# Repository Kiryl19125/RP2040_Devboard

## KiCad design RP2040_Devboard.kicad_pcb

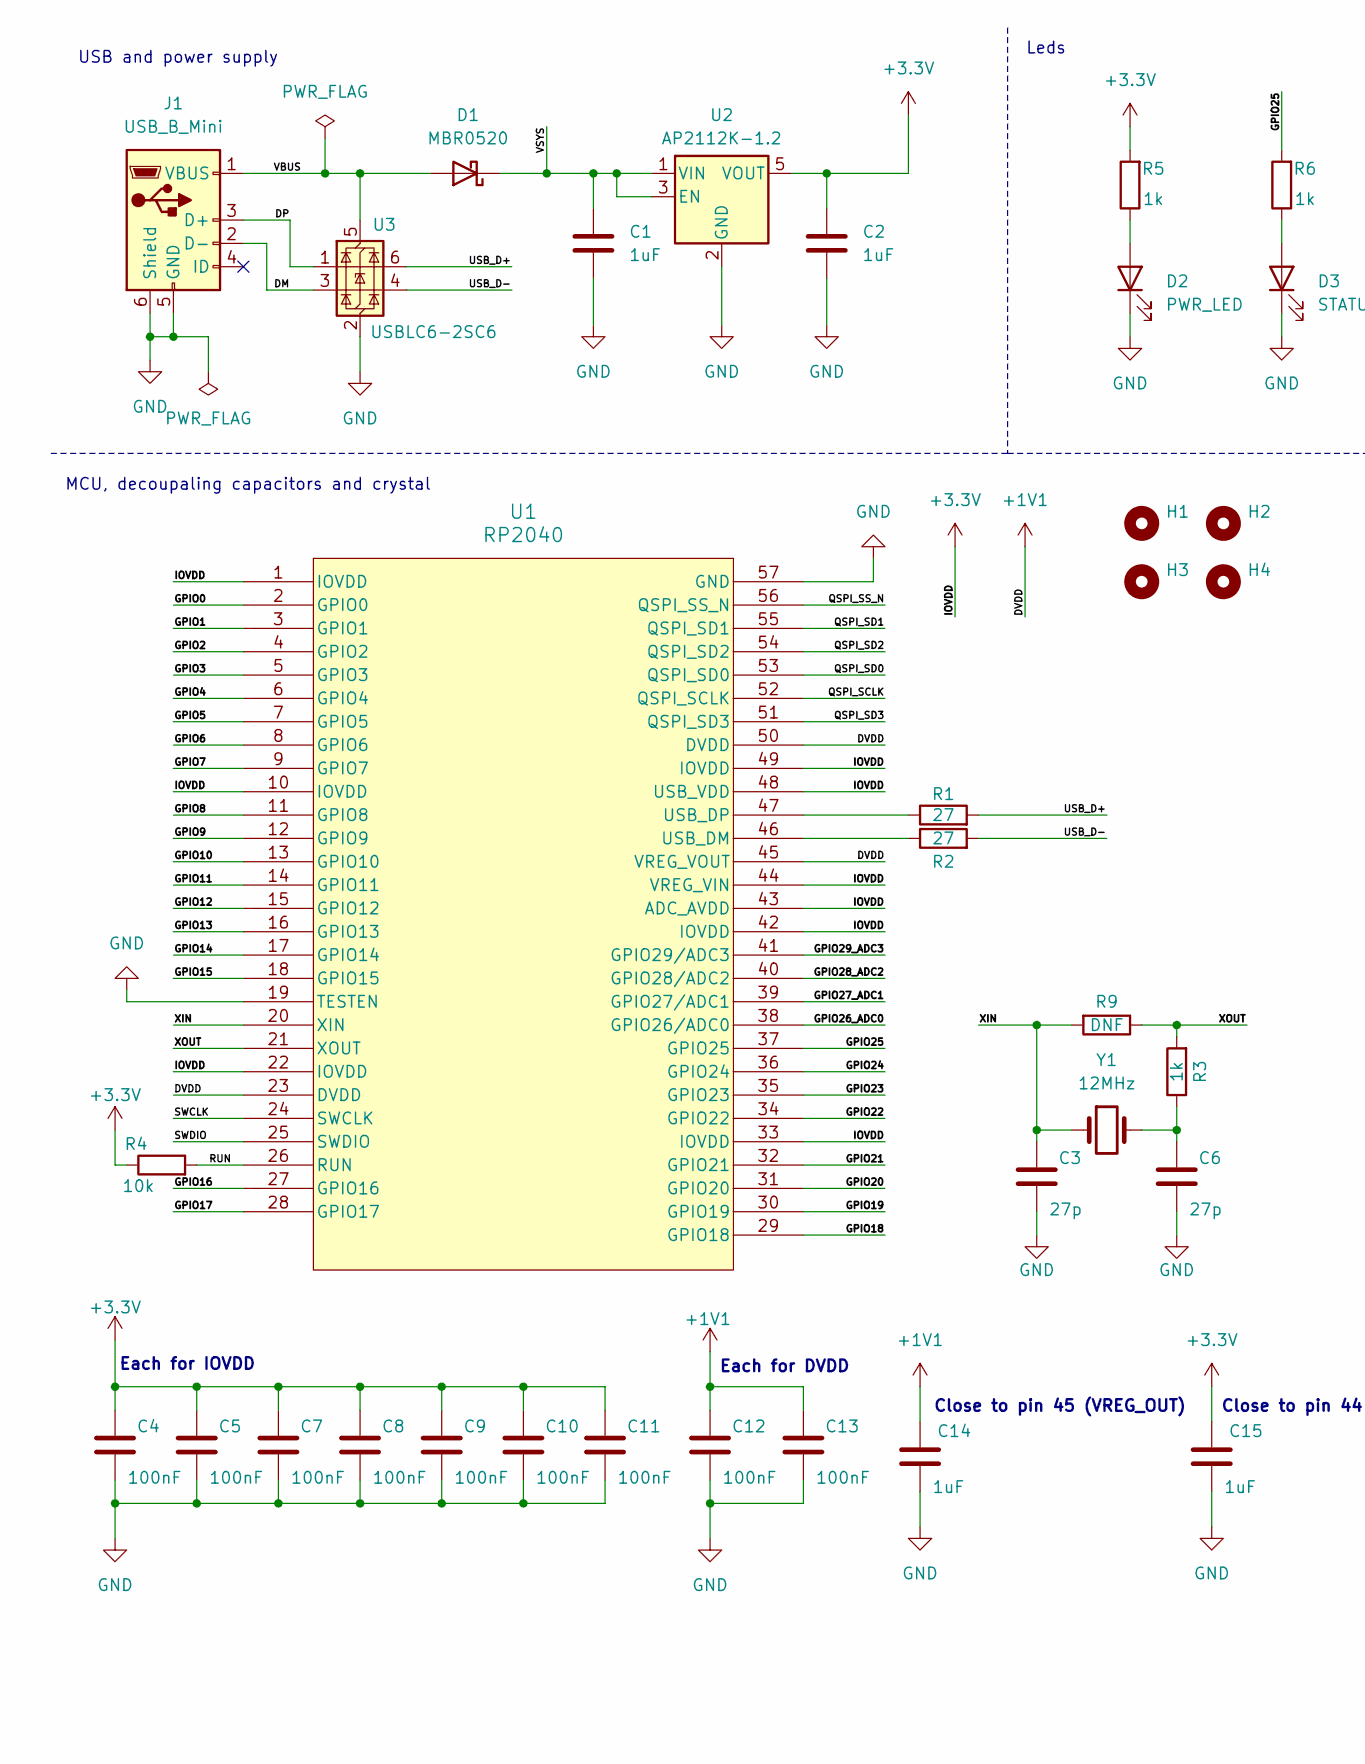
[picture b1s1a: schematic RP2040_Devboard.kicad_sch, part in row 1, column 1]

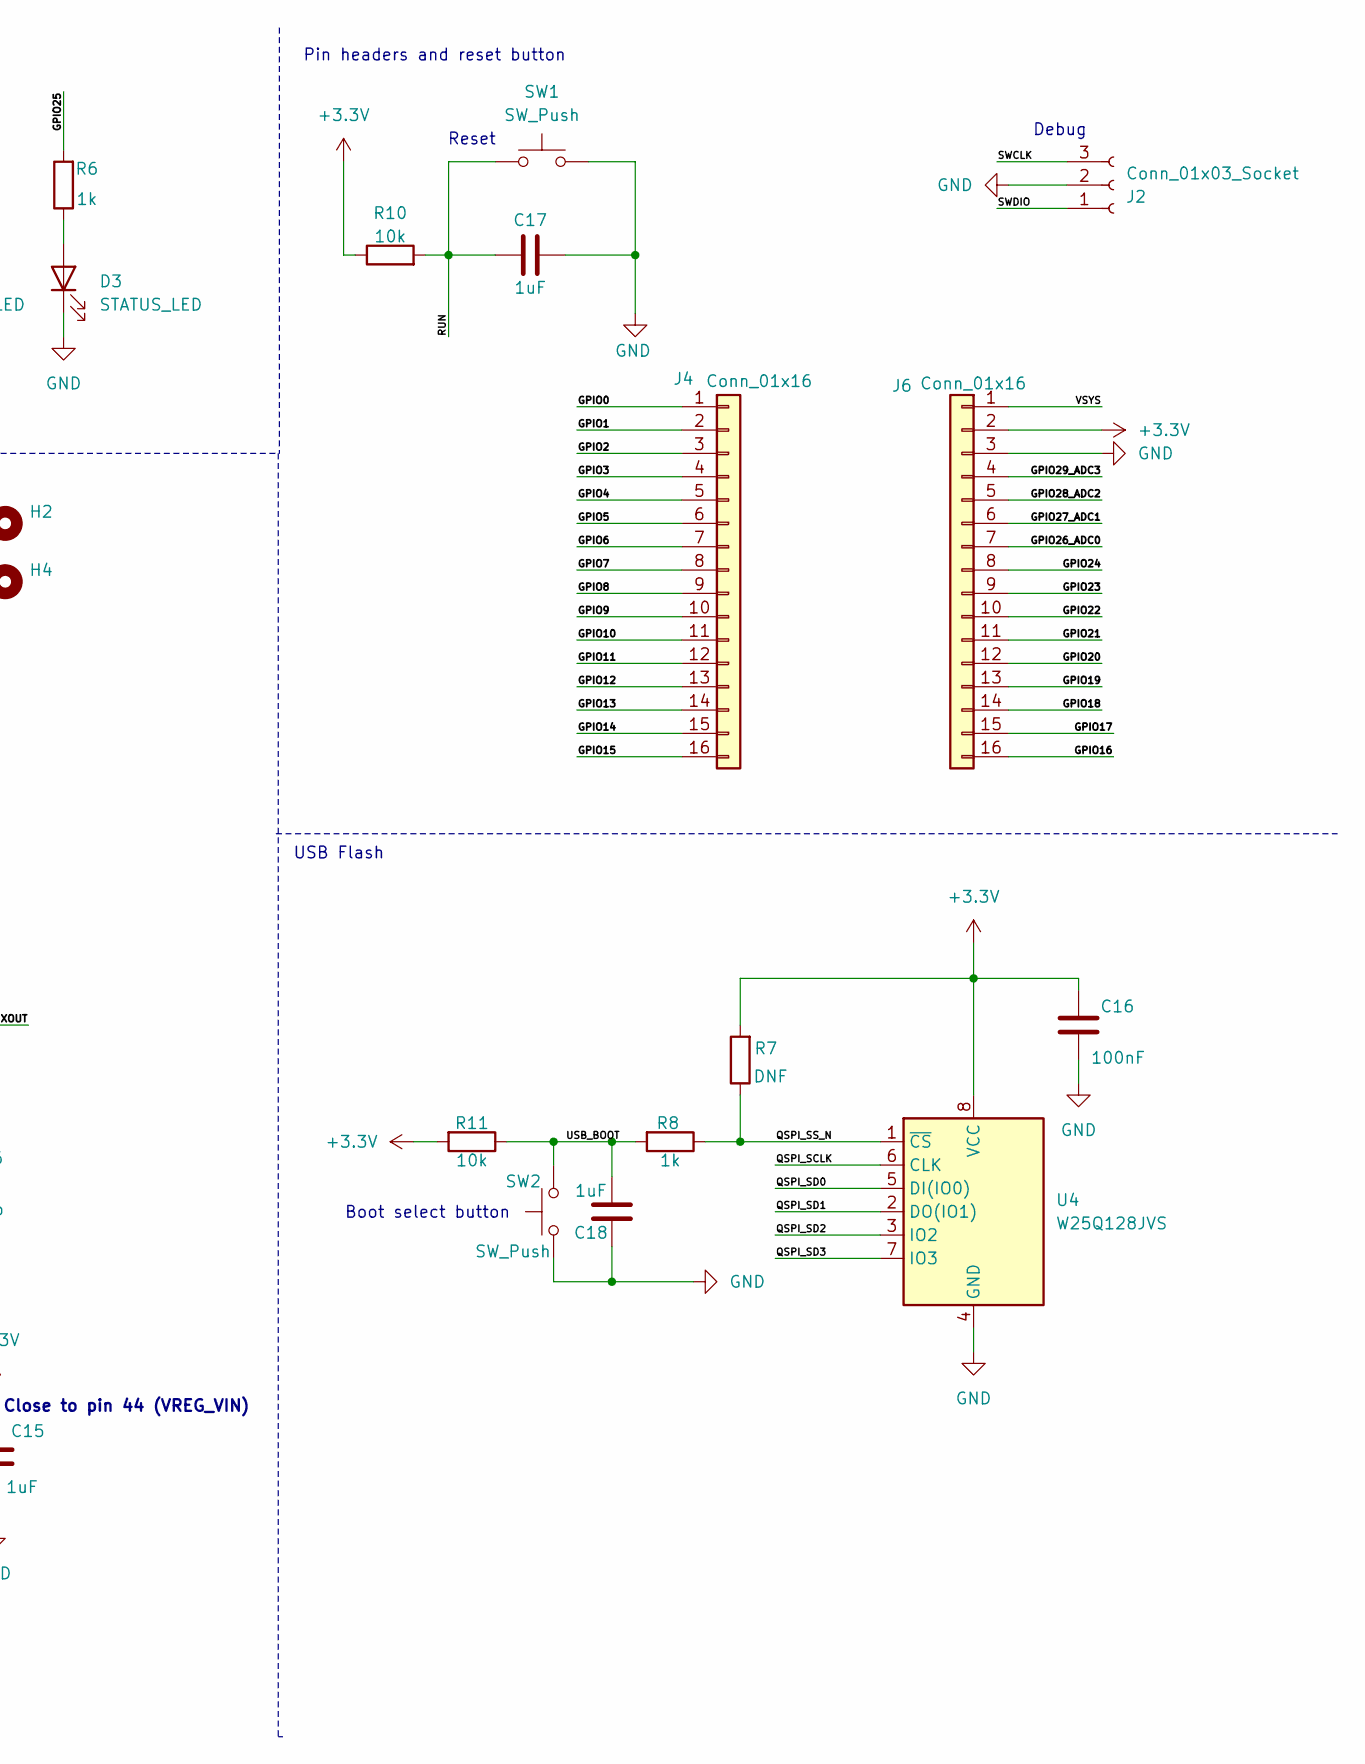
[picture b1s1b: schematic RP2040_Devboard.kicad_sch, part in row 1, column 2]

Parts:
C1, C2, C17, C18: 1uF; C_0805_2012Metric
C3, C6: 27p; C_0805_2012Metric
C4, C5, C7, C8, C9, C10, C11, C12, C13, C16: 100nF; C_0201_0603Metric
C14, C15: 1uF; C_0201_0603Metric
D1: MBR0520; D_SOD-123
D2: PWR_LED; LED_0805_2012Metric
D3: STATUS_LED; LED_0805_2012Metric
H1, H2, H3, H4: MountingHole; MountingHole_3mm
J1: USB_B_Mini; USB_Mini-B_Lumberg_2486_01_Horizontal
J2: Conn_01x03_Socket; PinHeader_1x03_P2.54mm_Vertical
J4, J6: Conn_01x16; PinSocket_1x16_P2.54mm_Vertical
R1, R2: 27; R_0201_0603Metric
R3, R5, R6: 1k; R_0805_2012Metric
R4: 10k; R_0201_0603Metric
R7: DNF; R_0201_0603Metric
R8: 1k; R_0201_0603Metric
R9: DNF; R_0805_2012Metric
R10, R11: 10k; R_0805_2012Metric
SW1, SW2: SW_Push; SW_SPST_PTS645
U1: RP2040; IC57_RP2040
U2: AP2112K-1.2; SOT-23-5
U3: USBLC6-2SC6; SOT-23-6
U4: W25Q128JVS; SOIC-8_5.23x5.23mm_P1.27mm
Y1: 12MHz; XTAL_HC49SM_MTC

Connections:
+1V1: C12.1, C13.1, C14.1, U1.23 (DVDD), U1.45 (VREG_VOUT), U1.50 (DVDD)
+3.3V: C2.1, C4.1, C5.1, C7.1, C8.1, C9.1, C10.1, C11.1, C15.1, C16.1, J6.2, R4.1, R5.2, R7.2, R10.1, R11.2, U1.1 (IOVDD), U1.10 (IOVDD), U1.22 (IOVDD), U1.33 (IOVDD), U1.42 (IOVDD), U1.43 (ADC_AVDD), U1.44 (VREG_VIN), U1.48 (USB_VDD), U1.49 (IOVDD), U2.5 (VOUT), U4.8 (VCC)
/DM: J1.2 (D-), U3.3 (I/O2)
/DP: J1.3 (D+), U3.1 (I/O1)
/GPIO0: J4.1, U1.2 (GPIO0)
/GPIO1: J4.2, U1.3 (GPIO1)
/GPIO2: J4.3, U1.4 (GPIO2)
/GPIO3: J4.4, U1.5 (GPIO3)
/GPIO4: J4.5, U1.6 (GPIO4)
/GPIO5: J4.6, U1.7 (GPIO5)
/GPIO6: J4.7, U1.8 (GPIO6)
/GPIO7: J4.8, U1.9 (GPIO7)
/GPIO8: J4.9, U1.11 (GPIO8)
/GPIO9: J4.10, U1.12 (GPIO9)
/GPIO10: J4.11, U1.13 (GPIO10)
/GPIO11: J4.12, U1.14 (GPIO11)
/GPIO12: J4.13, U1.15 (GPIO12)
/GPIO13: J4.14, U1.16 (GPIO13)
/GPIO14: J4.15, U1.17 (GPIO14)
/GPIO15: J4.16, U1.18 (GPIO15)
/GPIO16: J6.16, U1.27 (GPIO16)
/GPIO17: J6.15, U1.28 (GPIO17)
/GPIO18: J6.14, U1.29 (GPIO18)
/GPIO19: J6.13, U1.30 (GPIO19)
/GPIO20: J6.12, U1.31 (GPIO20)
/GPIO21: J6.11, U1.32 (GPIO21)
/GPIO22: J6.10, U1.34 (GPIO22)
/GPIO23: J6.9, U1.35 (GPIO23)
/GPIO24: J6.8, U1.36 (GPIO24)
/GPIO25: R6.2, U1.37 (GPIO25)
/GPIO26_ADC0: J6.7, U1.38 (GPIO26/ADC0)
/GPIO27_ADC1: J6.6, U1.39 (GPIO27/ADC1)
/GPIO28_ADC2: J6.5, U1.40 (GPIO28/ADC2)
/GPIO29_ADC3: J6.4, U1.41 (GPIO29/ADC3)
/QSPI_SCLK: U1.52 (QSPI_SCLK), U4.6 (CLK)
/QSPI_SD0: U1.53 (QSPI_SD0), U4.5 (DI(IO0))
/QSPI_SD1: U1.55 (QSPI_SD1), U4.2 (DO(IO1))
/QSPI_SD2: U1.54 (QSPI_SD2), U4.3 (IO2)
/QSPI_SD3: U1.51 (QSPI_SD3), U4.7 (IO3)
/QSPI_SS_N: R7.1, R8.1, U1.56 (QSPI_SS_N), U4.1 (~CS)
/RUN: C17.1, R4.2, R10.2, SW1.1, U1.26 (RUN)
/SWCLK: J2.3, U1.24 (SWCLK)
/SWDIO: J2.1, U1.25 (SWDIO)
/USB_BOOT: C18.1, R8.2, R11.1, SW2.2
/USB_D+: R1.2, U3.6 (I/O1)
/USB_D-: R2.2, U3.4 (I/O2)
/VBUS: D1.2 (A), J1.1 (VBUS), U3.5 (VBUS)
/VSYS: C1.1, D1.1 (K), J6.1, U2.1 (VIN), U2.3 (EN)
/XIN: C3.1, R9.2, U1.20 (XIN), Y1.1
/XOUT: R3.2, R9.1, U1.21 (XOUT)
GND: C1.2, C2.2, C3.2, C4.2, C5.2, C6.2, C7.2, C8.2, C9.2, C10.2, C11.2, C12.2, C13.2, C14.2, C15.2, C16.2, C17.2, C18.2, D2.1 (K), D3.1 (K), J1.5 (GND), J1.6 (Shield), J2.2, J6.3, SW1.2, SW2.1, U1.19 (TESTEN), U1.57 (GND), U2.2 (GND), U3.2 (GND), U4.4 (GND)
unnamed: C6.1, R3.1, Y1.2
unnamed: D2.2 (A), R5.1
unnamed: D3.2 (A), R6.1
unnamed: R2.1, U1.46 (USB_DM)
unnamed: R1.1, U1.47 (USB_DP)

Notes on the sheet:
USB and power supply
Each for DVDD
Boot select button
Debug
Pin headers and reset button
USB Flash
MCU, decoupaling capacitors and crystal
Leds
Close to pin 45 (VREG_OUT)
Each for IOVDD
Close to pin 44 (VREG_VIN)
Reset

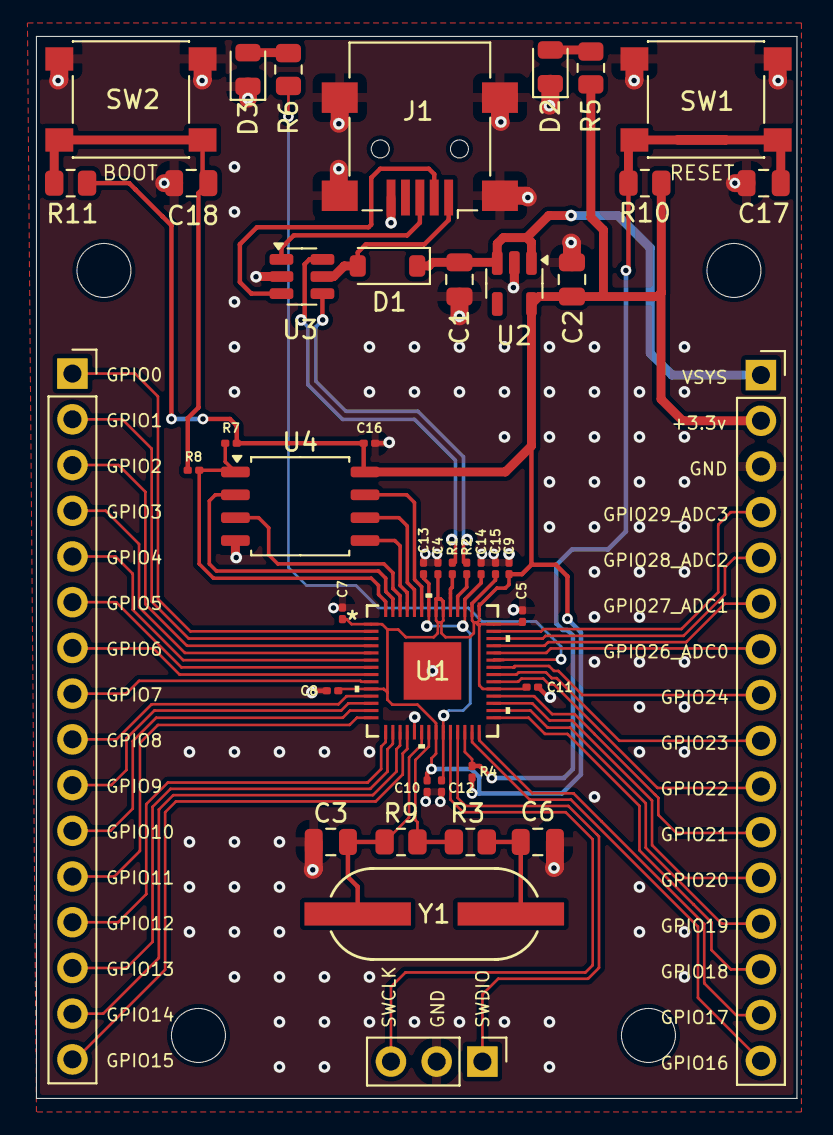
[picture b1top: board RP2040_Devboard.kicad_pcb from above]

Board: 2 copper layers, 42.2 x 59.0 mm, 47 parts (0 on the bottom side), 56 nets.

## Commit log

2024-11-16 Added board
2024-11-17 Added gnd zone on top layer
2024-11-18 Some lauayt changes
2024-11-21 Added RC for each button, deleted extra pins
2024-11-21 Better vias
2024-11-21 Added mointing holes and stetching vias
2024-11-21 Added board version
